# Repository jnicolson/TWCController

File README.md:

# TWCController
Wireless Controller for a Gen 2 Tesla Wall Charger (hardware and software)

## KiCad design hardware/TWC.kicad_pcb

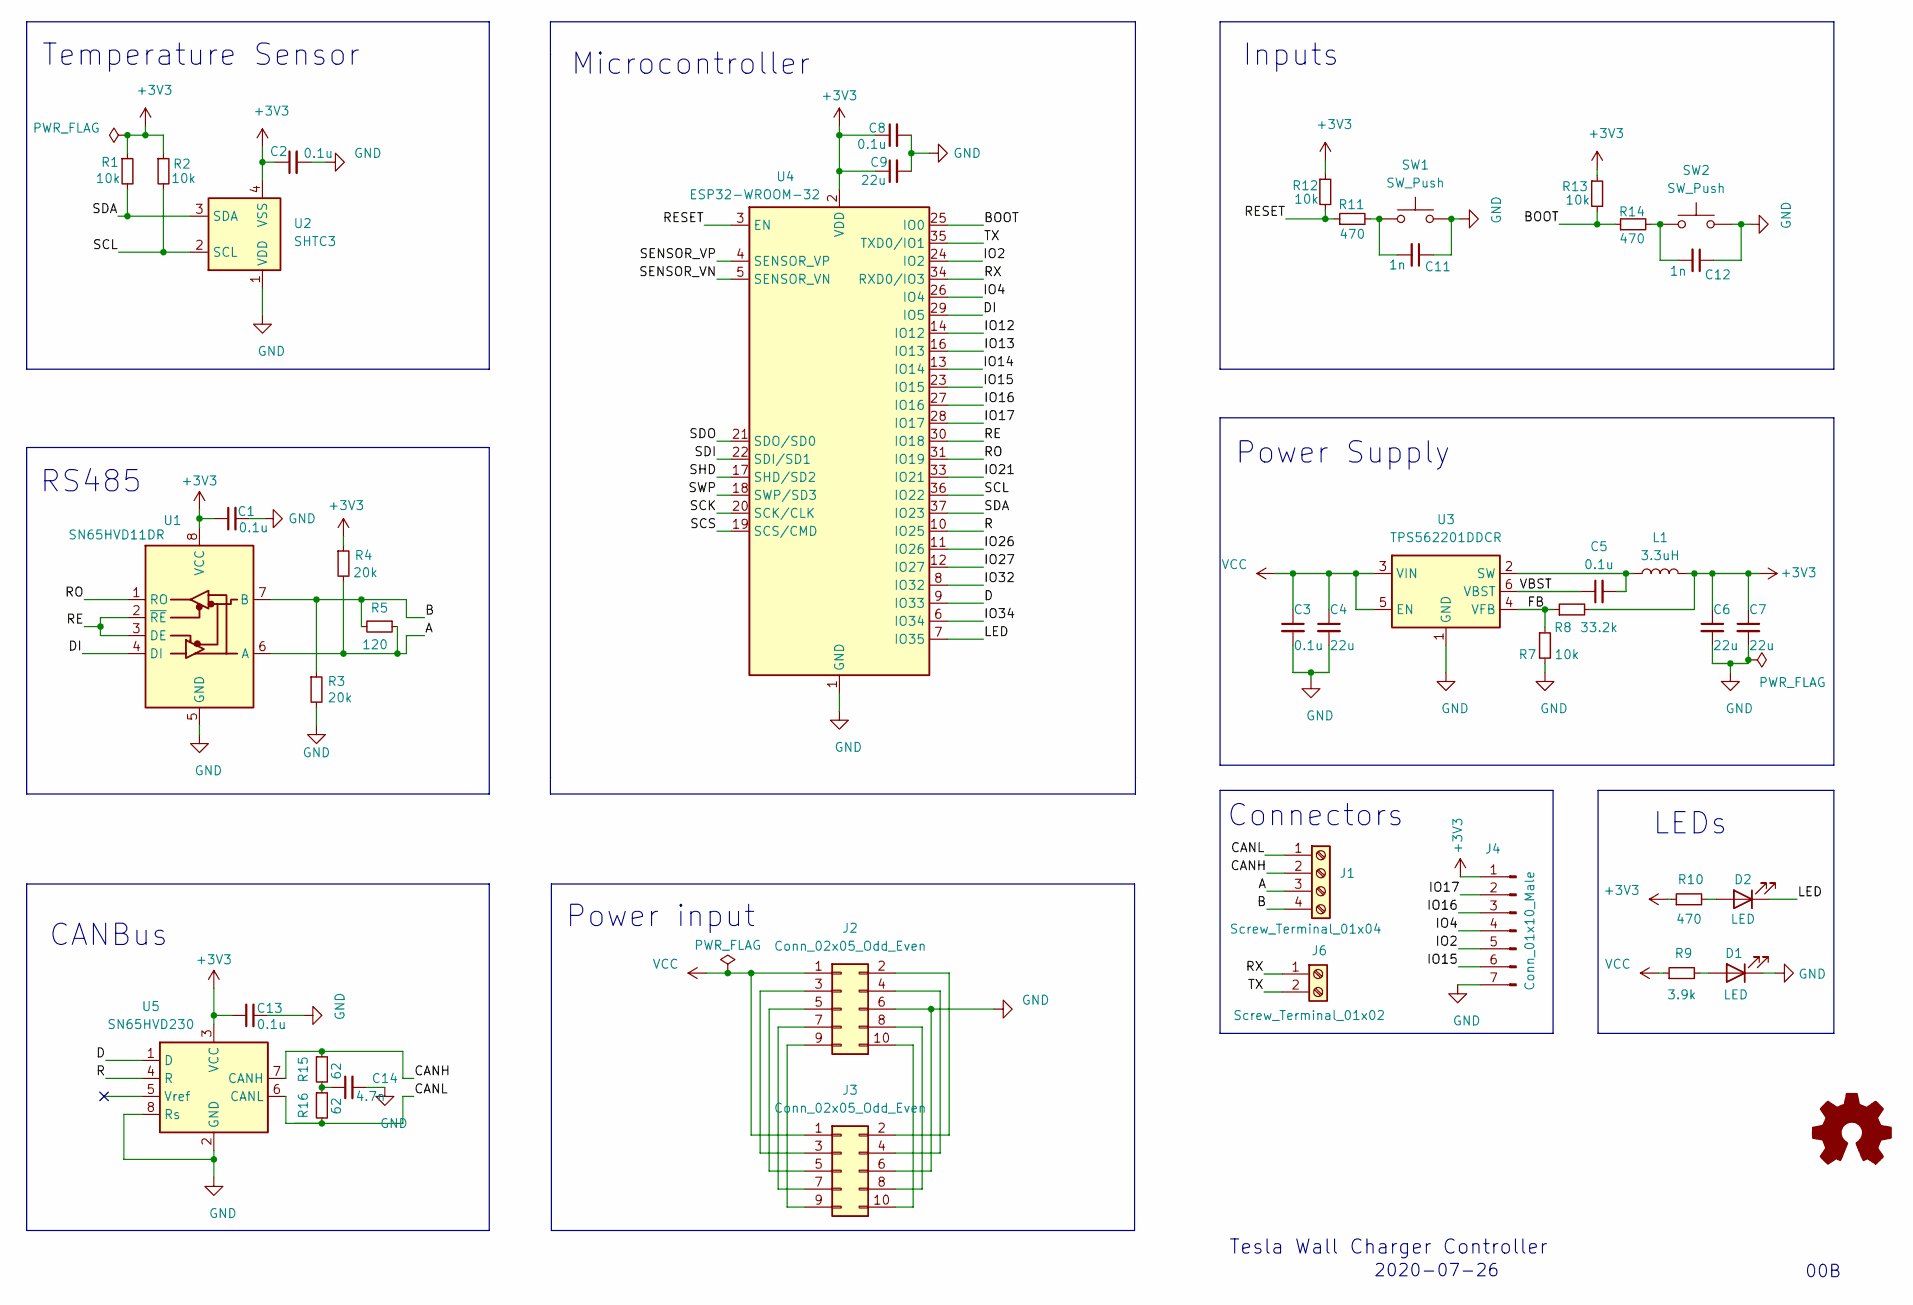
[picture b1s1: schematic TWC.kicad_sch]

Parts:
C1, C2, C3, C5, C8, C13: 0.1u; C_0603_1608Metric
C4, C6, C7, C9: 22u; C_0805_2012Metric
C11, C12: 1n; C_0603_1608Metric
C14: 4.7n; C_0603_1608Metric
D1, D2: LED; C_0603_1608Metric
J1: Screw_Terminal_01x04; Altech_AK500_1x04_P5.00
J2: Conn_02x05_Odd_Even; IDC-Header_2x05_P2.54mm_Vertical; Part Number SFH11-PBPC-D05-ST-BK
J3: Conn_02x05_Odd_Even; IDC-Header_2x05_P2.54mm_Vertical
J4: Conn_01x10_Male; PinHeader_1x07_P2.54mm_Vertical
J6: Screw_Terminal_01x02; Altech_AK500_1x02_P5.00
L1: 3.3uH; L_Taiyo-Yuden_NR-30xx
R1, R2, R7, R11, R13: 10k; R_0603_1608Metric
R3, R4: 20k; R_0603_1608Metric
R5: 120; R_0603_1608Metric
R8: 33.2k; R_0603_1608Metric
R9: 3.9k; R_0603_1608Metric
R10, R12, R14: 470; R_0603_1608Metric
R15, R16: 62; R_0603_1608Metric
SW1, SW2: SW_Push; SW_SPST_TS_1101_X_X
U1: SN65HVD11DR; SOIC-8_3.9x4.9mm_P1.27mm
U2: SHTC3; Sensirion_DFN-4-1EP_2x2mm_P1mm_EP0.7x1.6mm
U3: TPS562201DDCR; SOT-23-6
U4: ESP32-WROOM-32
U5: SN65HVD230; SOIC-8_3.9x4.9mm_P1.27mm

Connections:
+3V3: C1.1, C2.1, C6.1, C7.1, C8.1, C9.1, C13.1, J4.1, L1.2, R1.1, R2.1, R4.1, R8.2, R10.1, R11.1, R13.1, U1.8 (VCC), U2.4 (VSS), U4.2 (VDD), U5.3 (VCC)
/A: J1.3, R4.2, R5.1, U1.6 (A)
/B: J1.4, R3.1, R5.2, U1.7 (B)
/BOOT: R13.2, R14.1, U4.25 (IO0)
/CANH: J1.2, R15.1, U5.7 (CANH)
/CANL: J1.1, R16.2, U5.6 (CANL)
/D: U4.9 (IO33), U5.1 (D)
/DI: U1.4 (DI), U4.29 (IO5)
/FB: R7.1, R8.1, U3.4 (VFB)
/IO2: J4.5, U4.24 (IO2)
/IO4: J4.4, U4.26 (IO4)
/IO12: U4.14 (IO12)
/IO13: U4.16 (IO13)
/IO14: U4.13 (IO14)
/IO15: J4.6, U4.23 (IO15)
/IO16: J4.3, U4.27 (IO16)
/IO17: J4.2, U4.28 (IO17)
/IO21: U4.33 (IO21)
/IO26: U4.11 (IO26)
/IO27: U4.12 (IO27)
/IO32: U4.8 (IO32)
/IO34: U4.6 (IO34)
/LED: D2.1 (K), U4.7 (IO35)
/R: U4.10 (IO25), U5.4 (R)
/RE: U1.2 (~RE), U1.3 (DE), U4.30 (IO18)
/RESET: R11.2, R12.1, U4.3 (EN)
/RO: U1.1 (RO), U4.31 (IO19)
/RX: J6.1, U4.34 (RXD0/IO3)
/SCK: U4.20 (SCK/CLK)
/SCL: R2.2, U2.2 (SCL), U4.36 (IO22)
/SCS: U4.19 (SCS/CMD)
/SDA: R1.2, U2.3 (SDA), U4.37 (IO23)
/SDI: U4.22 (SDI/SD1)
/SDO: U4.21 (SDO/SD0)
/SENSOR_VN: U4.5 (SENSOR_VN)
/SENSOR_VP: U4.4 (SENSOR_VP)
/SHD: U4.17 (SHD/SD2)
/SWP: U4.18 (SWP/SD3)
/TX: J6.2, U4.35 (TXD0/IO1)
/VBST: C5.1, U3.6 (VBST)
GND: C1.2, C2.2, C3.2, C4.2, C6.2, C7.2, C8.2, C9.2, C11.1, C12.1, C13.2, C14.2, D1.1 (K), J2.6, J3.6, J4.7, R3.2, R7.2, SW1.2, SW2.2, U1.5 (GND), U2.1 (VDD), U3.1 (GND), U4.1 (GND), U4.15 (GND), U4.38 (GND), U4.39 (GND), U5.2 (GND), U5.8 (Rs)
unnamed: C5.2, L1.1, U3.2 (SW)
unnamed: C11.2, R12.2, SW1.1
unnamed: C12.2, R14.2, SW2.1
unnamed: C14.1, R15.2, R16.1
unnamed: D1.2 (A), R9.2
unnamed: D2.2 (A), R10.2
unnamed: J2.2, J3.2
unnamed: J2.3, J3.3
unnamed: J2.4, J3.4
unnamed: J2.5, J3.5
unnamed: J2.7, J3.7
unnamed: J2.8, J3.8
unnamed: J2.9, J3.9
unnamed: J2.10, J3.10
VCC: C3.1, C4.1, J2.1, J3.1, R9.1, U3.3 (VIN), U3.5 (EN)

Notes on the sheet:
RS485
Temperature Sensor
CANBus
Power input
Microcontroller
Connectors
Power Supply
Inputs
2020-07-26
Tesla Wall Charger Controller
LEDs
00B

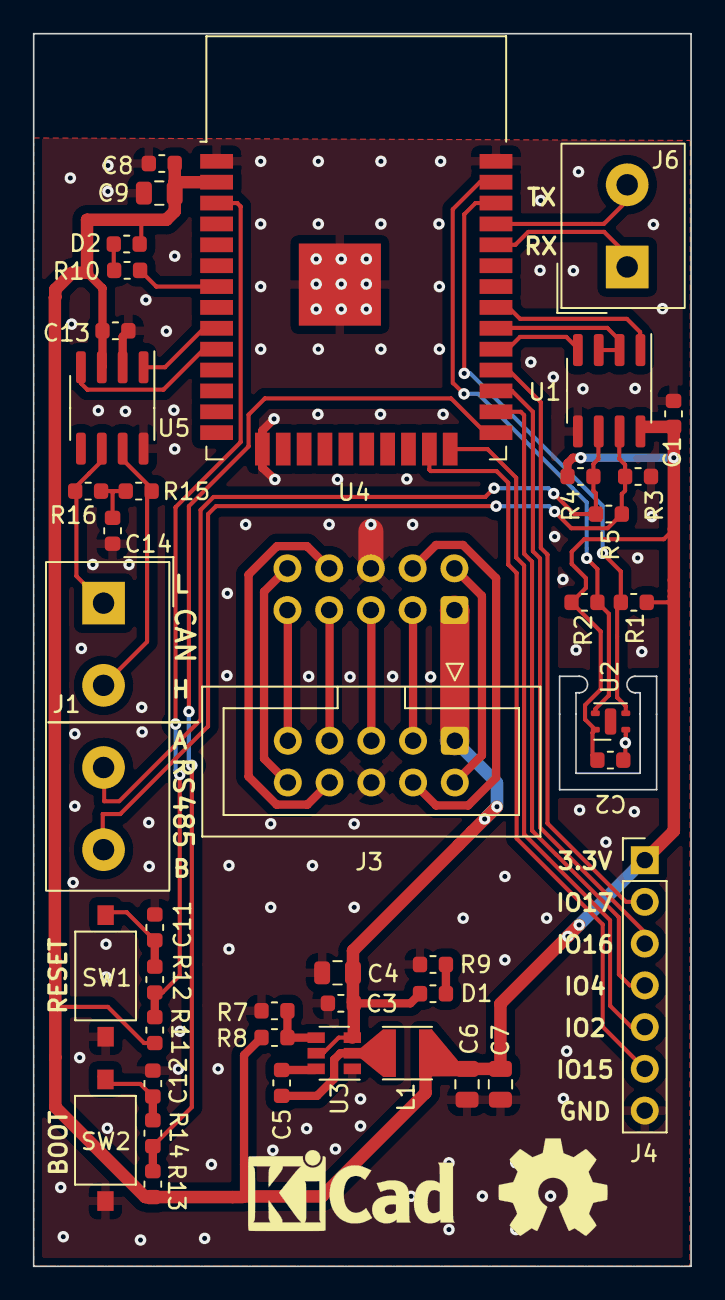
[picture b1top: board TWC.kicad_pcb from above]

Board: 2 copper layers, 40.0 x 75.0 mm, 43 parts (1 on the bottom side), 40 nets.

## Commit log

2020-07-26 Add KiCAD gitignore
2020-07-26 KiCAD project files with Schematic and PCB layout at Revision 00A
2020-07-26 Add PDF versions of Schematic and PCB Layers
2020-08-04 Many small updates, including changing the Buck Converter and temperature sensor to more available parts, changed the screw terminals to the final footprint (0.1" pitch)
2020-08-07 Revision 00B with added logos, small cosmetic fixes
